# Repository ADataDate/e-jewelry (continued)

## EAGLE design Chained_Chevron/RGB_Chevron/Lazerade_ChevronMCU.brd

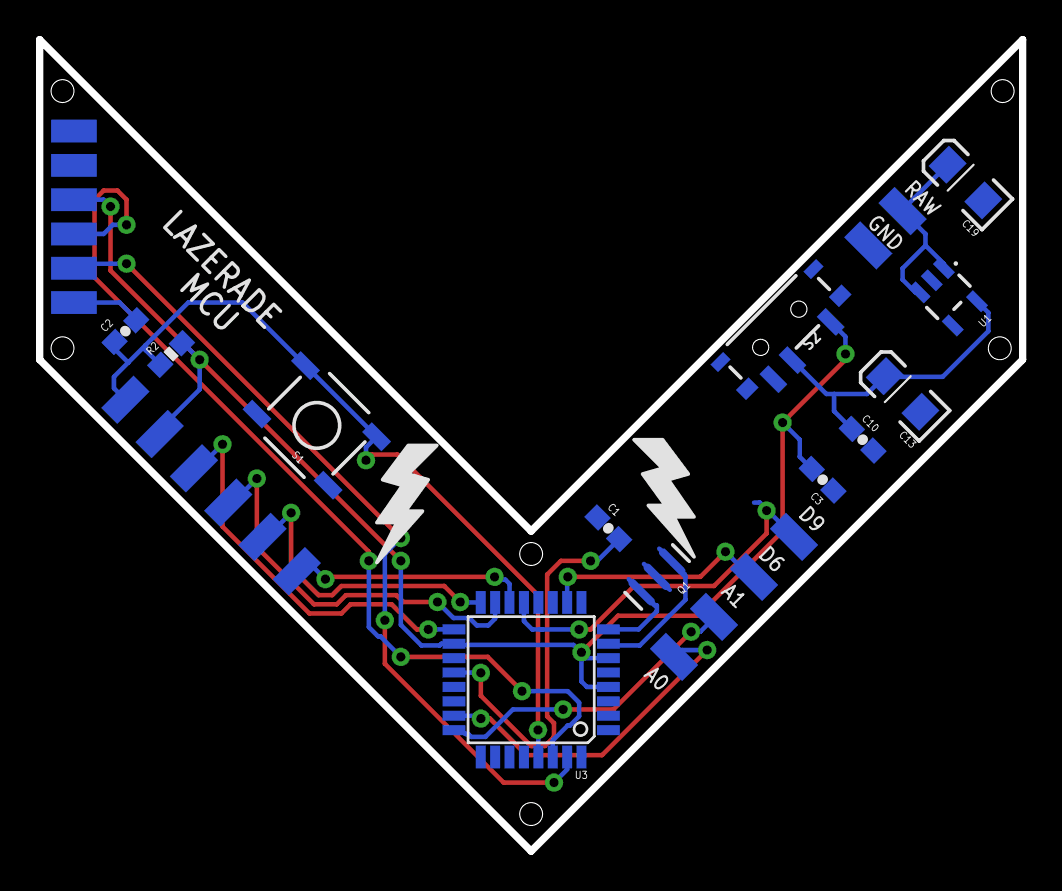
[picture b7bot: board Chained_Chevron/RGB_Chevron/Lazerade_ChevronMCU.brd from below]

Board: 2 copper layers, 54.6 x 45.1 mm, 31 parts (30 on the bottom side), 19 nets.

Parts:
C1, C2, C3, C10: 0.1uF; 0603-CAP
C13, C19: 10uF; EIA3216
FRAME1: FRAME-LETTER; CREATIVE_COMMONS
Q1: 8/16/20MHz; RESONATOR-SMD-1:1
R2: 10K; 0603-RES
S1: Reset; TACTILE-SWITCH-SMD-ALT01
S2: SWITCH_SPST_SMD_A
U1: 3.3V/150mA; SOT23-5
U3: ATMEGA328; TQFP32-08
U$1, U$2, U$3, U$4, U$5, U$6, U$7, U$8, U$9, U$10, U$11, U$12, U$13, U$14, U$15, U$16, U$17, U$18: LAZERADE_SINGLE_CONN; SINLGE_PAD_CONNECT

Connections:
A0: U3.23, U$1.P$1
A1: U3.24, U$2.P$1
AREF: C1.2, U3.20
D6: U3.10, U$3.P$1
D9: U3.13, U$4.P$1
D10: U3.14, U$11.P$1
DTR: C2.2, U$18.P$1
GND: C1.1, C3.1, C10.2, C13.C, C19.C, Q1.2, S1.1, S1.2, U1.2, U3.3, U3.5, U3.21, U$6.P$1, U$13.P$1, U$14.P$1
MISO: U3.16, U$9.P$1
MOSI: U3.15, U$10.P$1
unnamed: Q1.3, U3.8
unnamed: Q1.1, U3.7
RAW: C19.A, U1.1, U1.3, U$5.P$1
RESET: C2.1, R2.1, S1.3, S1.4, U3.29, U$12.P$1
RXI: U3.30, U$16.P$1
SCK: U3.17, U$8.P$1
TXO: U3.31, U$17.P$1
VCC: C3.2, R2.2, S2.3, U3.4, U3.6, U3.18, U$7.P$1, U$15.P$1
VOUT: C10.1, C13.A, S2.2, U1.5

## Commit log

2021-02-22 adding WIP
